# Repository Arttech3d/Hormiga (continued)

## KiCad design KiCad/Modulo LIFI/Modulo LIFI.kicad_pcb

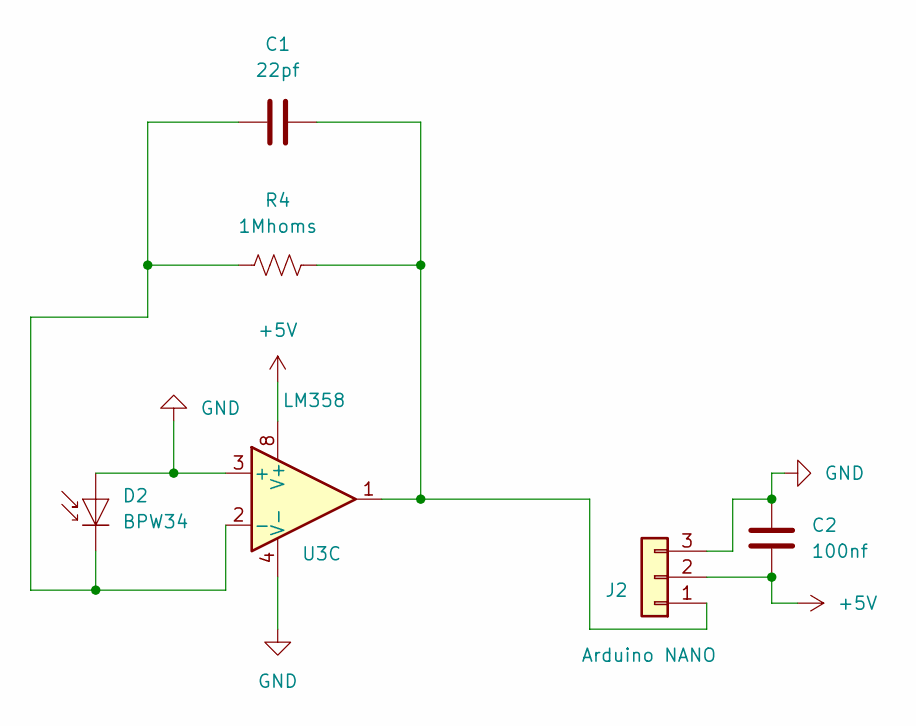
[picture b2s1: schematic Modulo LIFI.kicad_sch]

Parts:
C1: 22pf; C_Disc_D3.0mm_W1.6mm_P2.50mm
C2: 100nf; C_0805_2012Metric
D2: BPW34; Osram_BPW34S-SMD
J2: Arduino NANO; PinHeader_1x03_P2.54mm_Vertical
R4: 1Mhoms; R_0805_2012Metric_Pad1.20x1.40mm_HandSolder
U3: LM358; SOIC-8_3.9x4.9mm_P1.27mm

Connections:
+5V: C2.1, J2.2, U3.8 (V+)
GND: C2.2, D2.2 (A), J2.3, U3.3 (+), U3.4 (V-)
unnamed: C1.2, D2.1 (K), R4.2, U3.2 (-)
unnamed: C1.1, J2.1, R4.1, U3.1

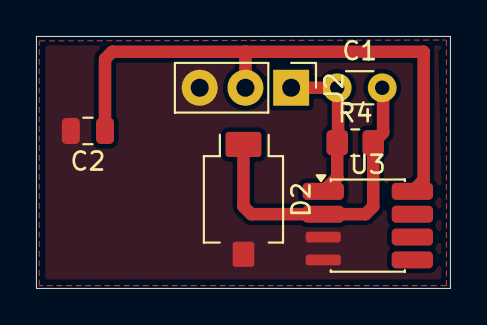
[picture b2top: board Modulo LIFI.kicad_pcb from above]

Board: 2 copper layers, 23.0 x 14.0 mm, 6 parts (0 on the bottom side), 4 nets.

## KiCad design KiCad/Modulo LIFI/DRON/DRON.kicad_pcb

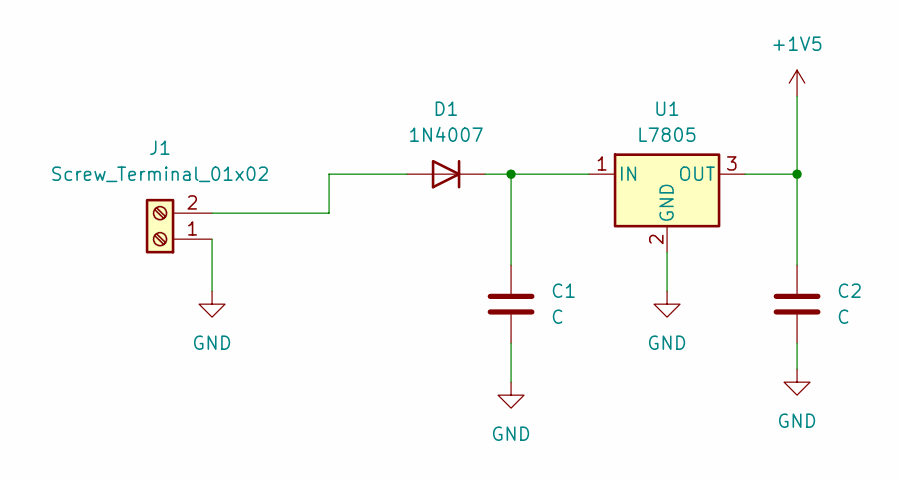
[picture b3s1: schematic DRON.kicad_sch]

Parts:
C1, C2: C; C_Disc_D3.0mm_W1.6mm_P2.50mm
D1: 1N4007; D_DO-41_SOD81_P10.16mm_Horizontal
J1: Screw_Terminal_01x02; TerminalBlock_MaiXu_MX126-5.0-02P_1x02_P5.00mm
U1: L7805; TO-220-3_Vertical

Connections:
+1V5: C2.1, U1.3 (OUT)
GND: C1.2, C2.2, J1.1, U1.2 (GND)
unnamed: D1.2 (A), J1.2
unnamed: C1.1, D1.1 (K), U1.1 (IN)

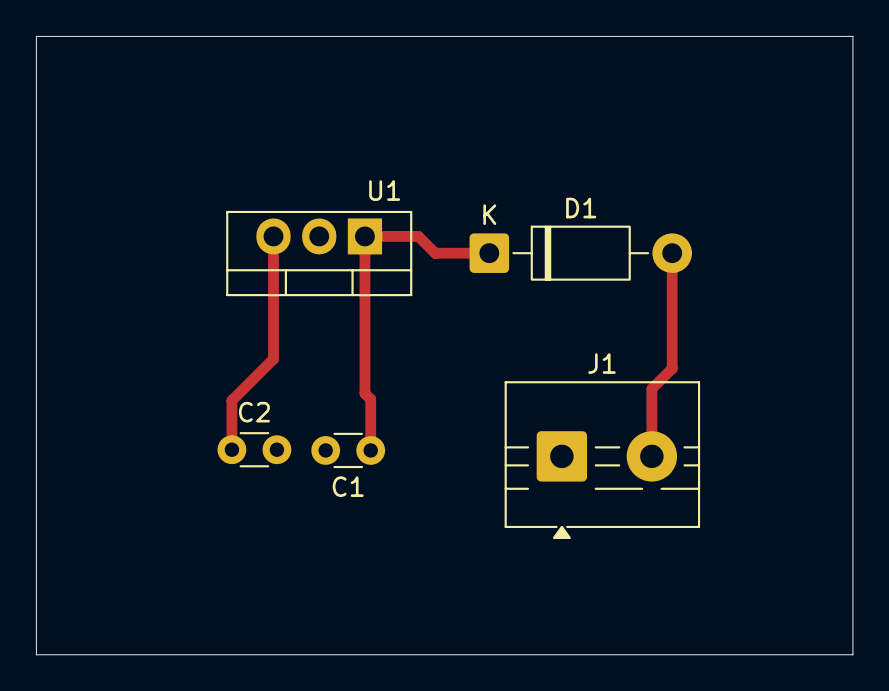
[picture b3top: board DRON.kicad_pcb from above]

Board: 2 copper layers, 45.4 x 34.4 mm, 5 parts (0 on the bottom side), 4 nets.

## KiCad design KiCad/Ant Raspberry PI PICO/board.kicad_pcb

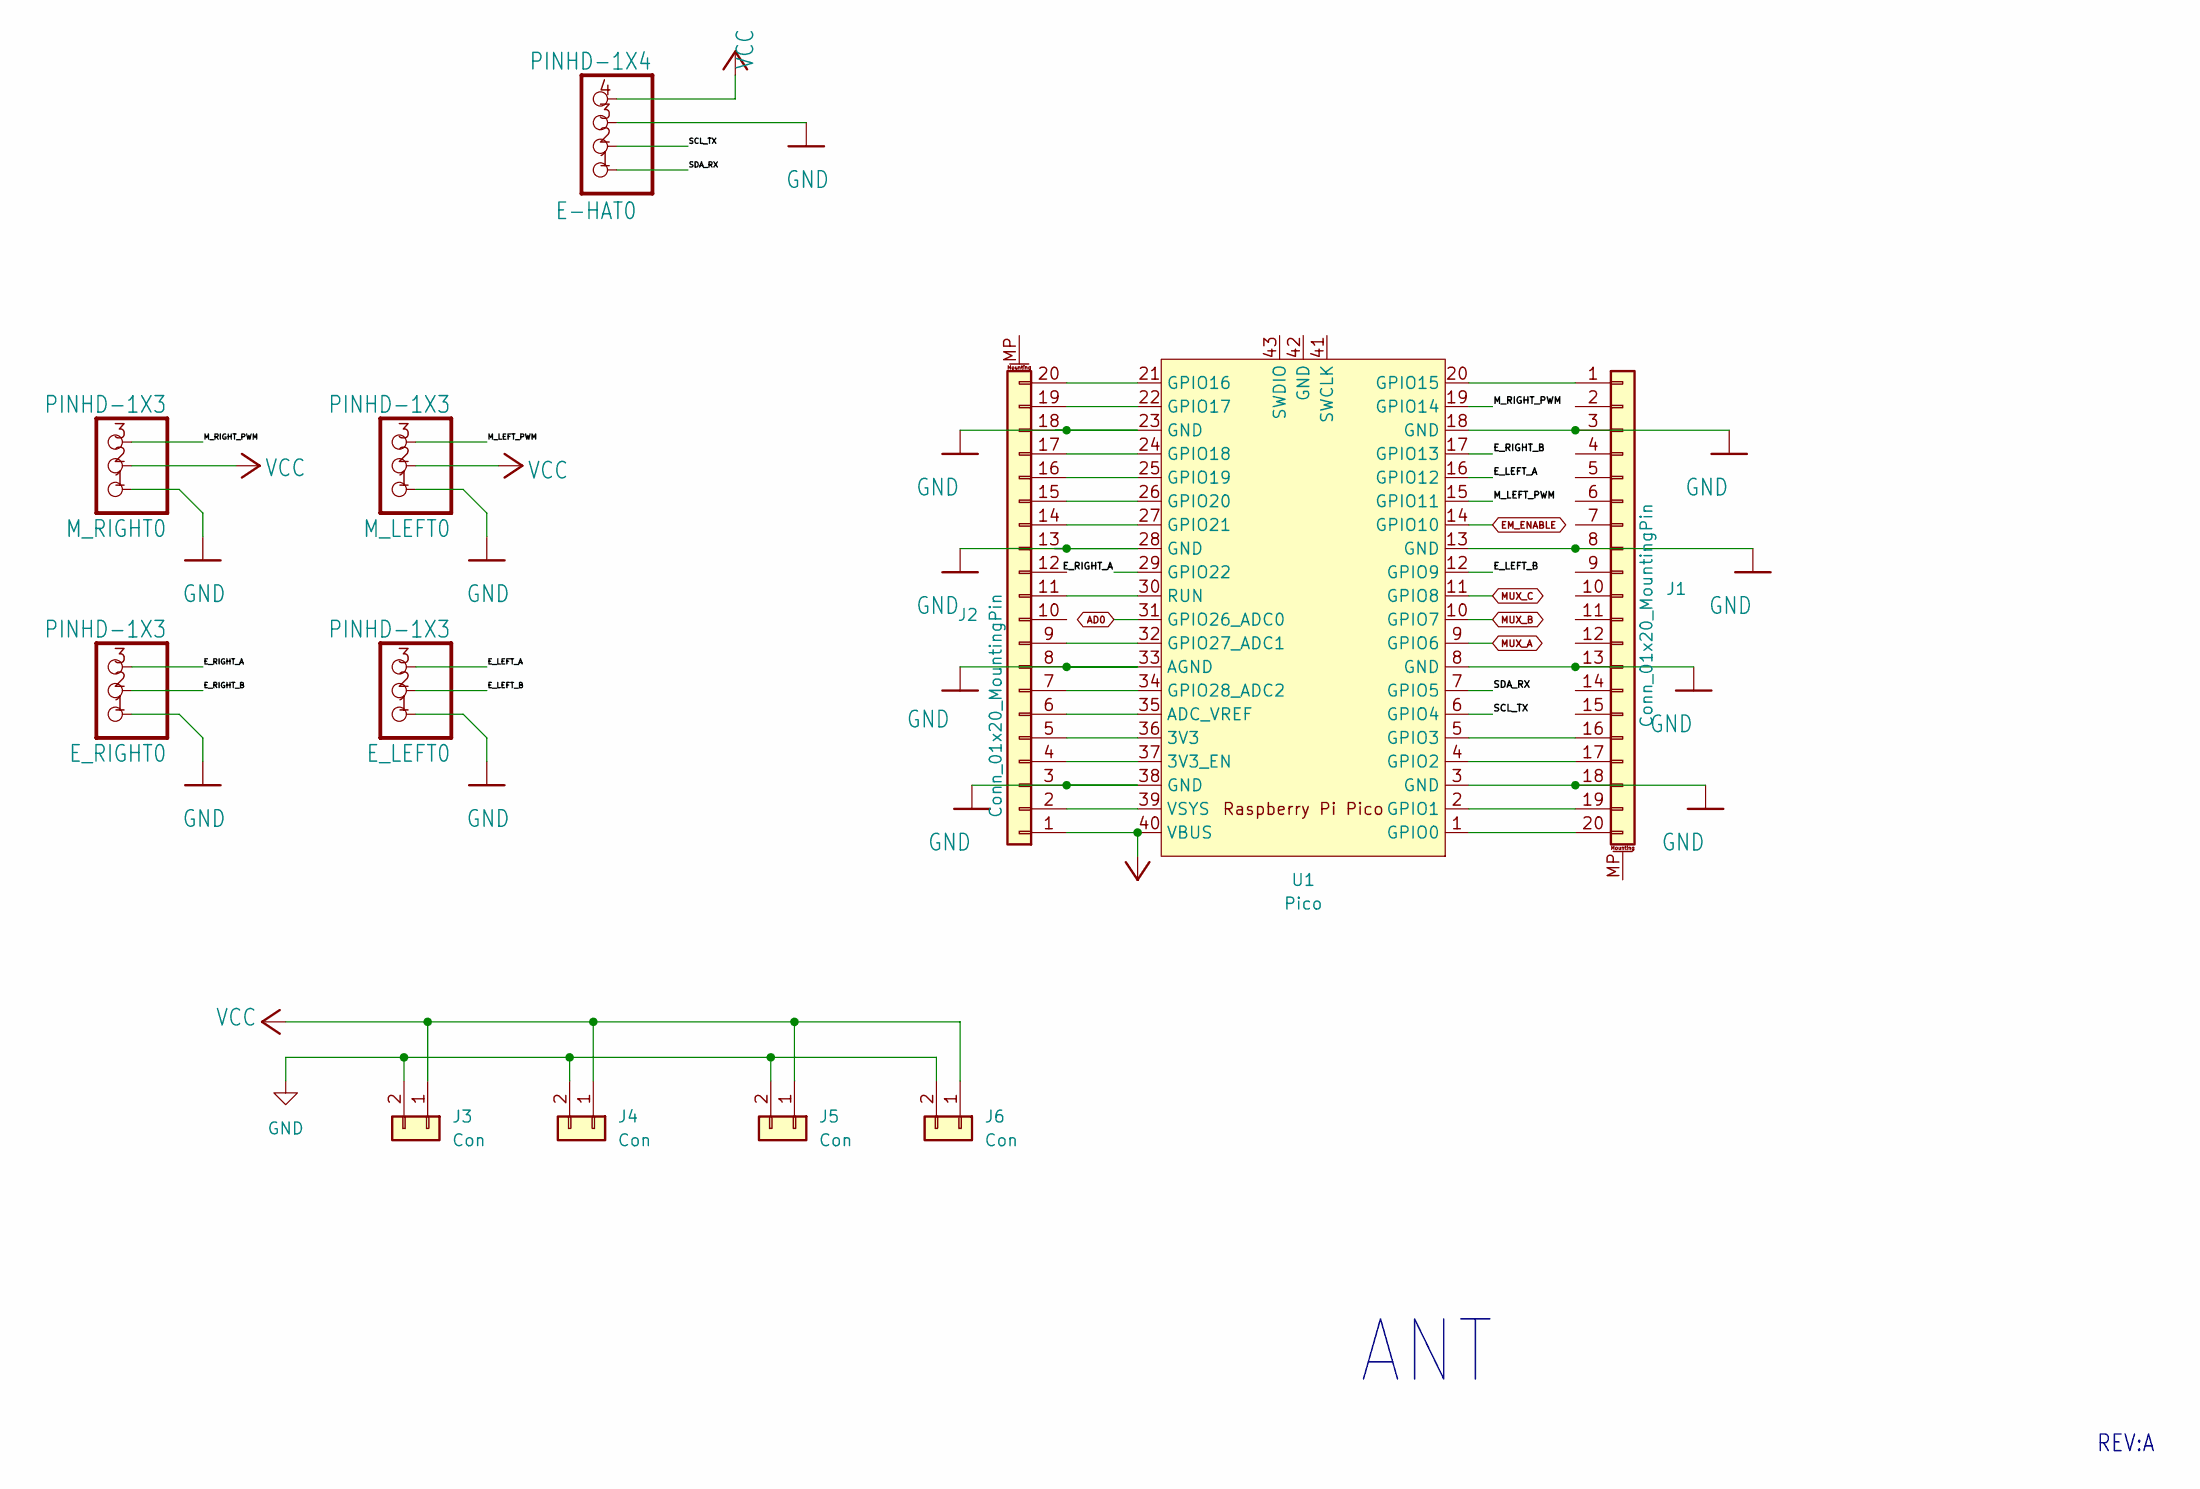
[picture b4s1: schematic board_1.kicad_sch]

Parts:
E-HAT0: PINHD-1X4; 1X04
E_LEFT0: PINHD-1X3; 1X03
E_RIGHT0: PINHD-1X3; 1X03
J1, J2: Conn_01x20_MountingPin; PinHeader_1x20_P2.54mm_Vertical
J3, J4, J5, J6: Con; PinHeader_1x02_P2.54mm_Vertical
M_LEFT0: PINHD-1X3; 1X03
M_RIGHT0: PINHD-1X3; 1X03
U1: Pico; RPi_Pico_SMD_TH

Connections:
/<p>MCU and Motors</p>/E_LEFT_A: E_LEFT0.3, U1.16 (GPIO12)
/<p>MCU and Motors</p>/E_LEFT_B: E_LEFT0.2, U1.12 (GPIO9)
/<p>MCU and Motors</p>/E_RIGHT_A: E_RIGHT0.3, U1.29 (GPIO22)
/<p>MCU and Motors</p>/E_RIGHT_B: E_RIGHT0.2, U1.17 (GPIO13)
/<p>MCU and Motors</p>/M_LEFT_PWM: M_LEFT0.3, U1.15 (GPIO11)
/<p>MCU and Motors</p>/M_RIGHT_PWM: M_RIGHT0.3, U1.19 (GPIO14)
/<p>MCU and Motors</p>/SCL_TX: E-HAT0.2, U1.6 (GPIO4)
/<p>MCU and Motors</p>/SDA_RX: E-HAT0.1, U1.7 (GPIO5)
AD0: U1.31 (GPIO26_ADC0); also elsewhere on the board
EM_ENABLE: U1.14 (GPIO10); also elsewhere on the board
GND: E-HAT0.3, E_LEFT0.1, E_RIGHT0.1, J1.3, J1.8, J1.13, J1.18, J2.3, J2.8, J2.13, J2.18, J3.2, J4.2, J5.2, J6.2, M_LEFT0.1, M_RIGHT0.1, U1.3 (GND), U1.8 (GND), U1.13 (GND), U1.18 (GND), U1.23 (GND), U1.28 (GND), U1.33 (AGND), U1.38 (GND); also elsewhere on the board
MUX_A: U1.9 (GPIO6); also elsewhere on the board
MUX_B: U1.10 (GPIO7); also elsewhere on the board
MUX_C: U1.11 (GPIO8); also elsewhere on the board
unnamed: J1.1, U1.20 (GPIO15)
unnamed: J1.16, U1.5 (GPIO3)
unnamed: J1.17, U1.4 (GPIO2)
unnamed: J1.19, U1.2 (GPIO1)
unnamed: J1.20, U1.1 (GPIO0)
unnamed: J2.2, U1.39 (VSYS)
unnamed: J2.4, U1.37 (3V3_EN)
unnamed: J2.5, U1.36 (3V3)
unnamed: J2.6, U1.35 (ADC_VREF)
unnamed: J2.7, U1.34 (GPIO28_ADC2)
unnamed: J2.9, U1.32 (GPIO27_ADC1)
unnamed: J2.11, U1.30 (RUN)
unnamed: J2.14, U1.27 (GPIO21)
unnamed: J2.15, U1.26 (GPIO20)
unnamed: J2.16, U1.25 (GPIO19)
unnamed: J2.17, U1.24 (GPIO18)
unnamed: J2.19, U1.22 (GPIO17)
unnamed: J2.20, U1.21 (GPIO16)
VCC: E-HAT0.4, J2.1, J3.1, J4.1, J5.1, J6.1, M_LEFT0.2, M_RIGHT0.2, U1.40 (VBUS); also elsewhere on the board

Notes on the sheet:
ANT
REV:A

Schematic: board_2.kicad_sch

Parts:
IRLML2502: MOSFET-NREFLOW; SOT23
MUX0: 4051D; SO16
P0, P1, P2, P3, P4, P5, P6, P7: TCRT5000
R0, R1, R2, R3, R4, R5, R6, R7: 4k7; M0805
R8: 4k7; R0805
R9: 0R; R0805
R10: 18R; R0805
R11: NM; R0805

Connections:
/<p>Proximity Sensors</p>/EM: P0.K (CATHODE), P1.K (CATHODE), P2.K (CATHODE), P3.K (CATHODE), P4.K (CATHODE), P5.K (CATHODE), P6.K (CATHODE), P7.K (CATHODE), R9.2, R11.2
/<p>Proximity Sensors</p>/MUX_X0: MUX0.13 (X0), P0.E (EMITTER), R4.1
/<p>Proximity Sensors</p>/MUX_X1: MUX0.14 (X1), P1.E (EMITTER), R5.1
/<p>Proximity Sensors</p>/MUX_X2: MUX0.15 (X2), P2.E (EMITTER), R6.1
/<p>Proximity Sensors</p>/MUX_X3: MUX0.12 (X3), P3.E (EMITTER), R3.1
/<p>Proximity Sensors</p>/MUX_X4: MUX0.1 (X4), P4.E (EMITTER), R7.1
/<p>Proximity Sensors</p>/MUX_X5: MUX0.5 (X5), P5.E (EMITTER), R2.1
/<p>Proximity Sensors</p>/MUX_X6: MUX0.2 (X6), P6.E (EMITTER), R0.1
/<p>Proximity Sensors</p>/MUX_X7: MUX0.4 (X7), P7.E (EMITTER), R1.1
AD0: MUX0.3 (X); also elsewhere on the board
EM_ENABLE: R8.2; also elsewhere on the board
GND: IRLML2502.2 (S), MUX0.6 (INH), MUX0.7 (VEE), MUX0.8 (GND), R0.2, R1.2, R2.2, R3.2, R4.2, R5.2, R6.2, R7.2; also elsewhere on the board
MUX_A: MUX0.11 (A); also elsewhere on the board
MUX_B: MUX0.10 (B); also elsewhere on the board
MUX_C: MUX0.9 (C); also elsewhere on the board
unnamed: IRLML2502.3 (D), R10.1
unnamed: IRLML2502.1 (G), R8.1
unnamed: R9.1, R10.2, R11.1
VCC: MUX0.16 (VCC), P0.A (ANODE), P0.C (COLLECTOR), P1.A (ANODE), P1.C (COLLECTOR), P2.A (ANODE), P2.C (COLLECTOR), P3.A (ANODE), P3.C (COLLECTOR), P4.A (ANODE), P4.C (COLLECTOR), P5.A (ANODE), P5.C (COLLECTOR), P6.A (ANODE), P6.C (COLLECTOR), P7.A (ANODE), P7.C (COLLECTOR); also elsewhere on the board

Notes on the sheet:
HeRo v2.7 VeRLab
REV:A

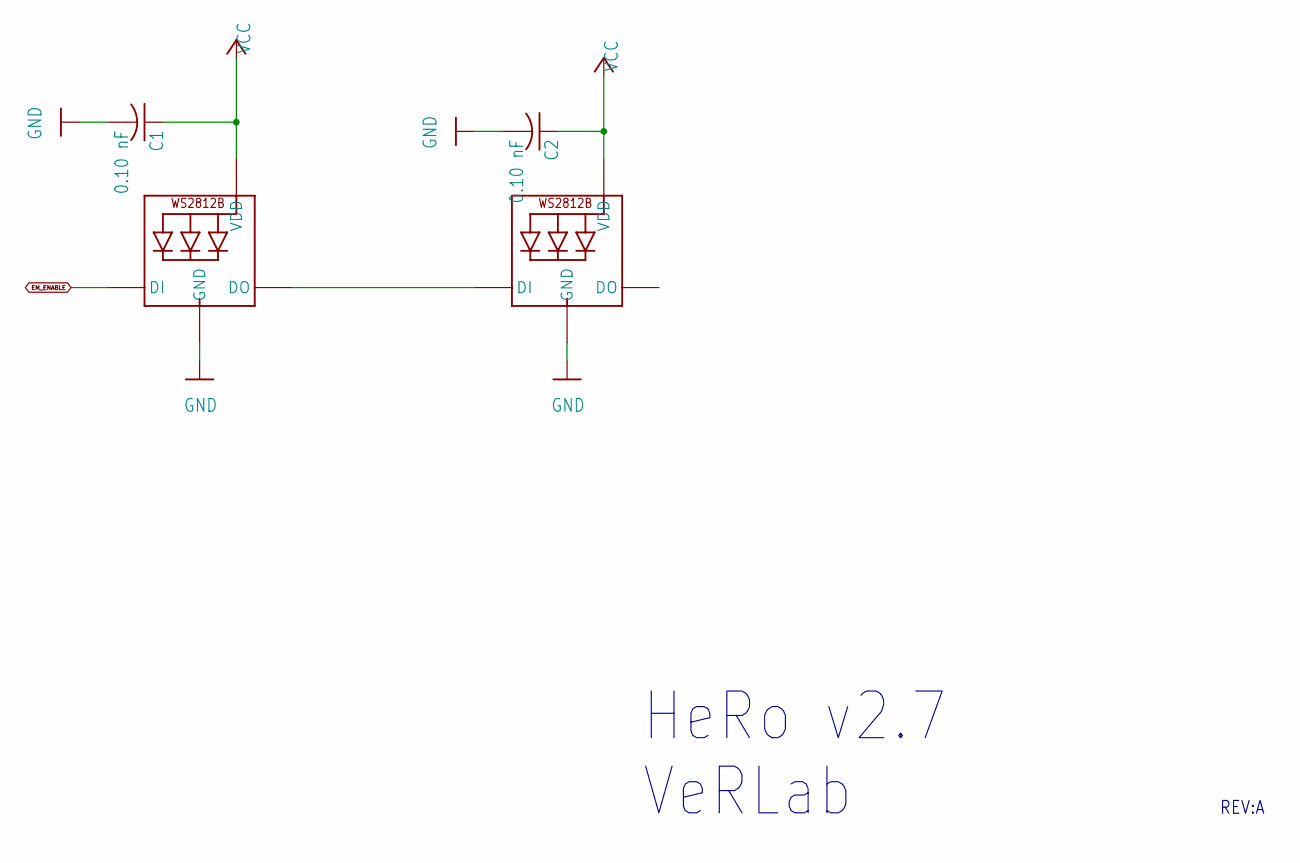
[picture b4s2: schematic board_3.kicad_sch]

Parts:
C1, C2: 0.10 nF; C0603_348
LED0, LED1: WS2812B5050; WS2812B

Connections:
EM_ENABLE: LED0.4-DIN (DI); also elsewhere on the board
GND: C1.2, C2.2, LED0.3-GND (GND), LED1.3-GND (GND); also elsewhere on the board
unnamed: LED0.2-DOUT (DO), LED1.4-DIN (DI)
VCC: C1.1, C2.1, LED0.1-VDD (VDD), LED1.1-VDD (VDD); also elsewhere on the board

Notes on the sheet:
HeRo v2.7 VeRLab
REV:A

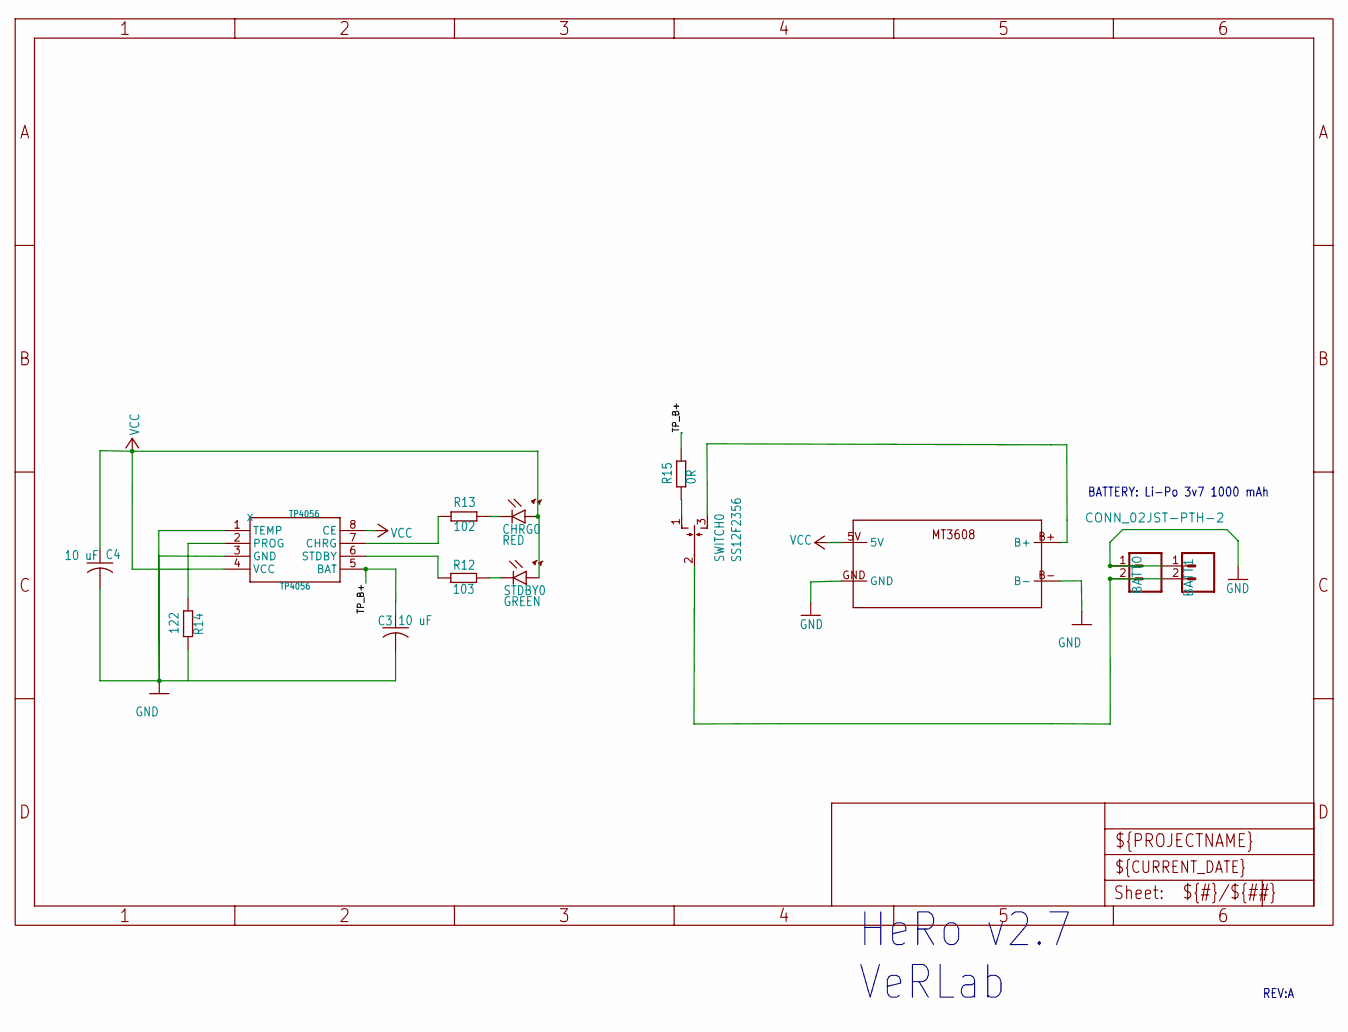
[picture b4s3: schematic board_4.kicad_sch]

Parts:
BATT0, BATT1: CONN_02JST-PTH-2; JST-2-PTH
C3, C4: 10 uF; C0603_420
CHRG0: RED; SML0805
MT3608: MT3608
R12: 103; R0805
R13: 102; R0805
R14: 122; R0603
R15: 0R; R0805
STDBY0: GREEN; SML0805
SWITCH0: SS12F2356; HH3T90
TP4056: TP4056; SOP

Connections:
/<p>Power Supply</p>/TP_B+: C3.1, R15.2, TP4056.5 (BAT)
GND: BATT0.1, BATT1.1, C3.2, C4.2, MT3608.B-, MT3608.GND, TP4056.1 (TEMP), TP4056.3 (GND); also elsewhere on the board
unnamed: CHRG0.C, R13.2
unnamed: R12.2, STDBY0.C
unnamed: R15.1, SWITCH0.1 (O)
unnamed: BATT0.2, BATT1.2, SWITCH0.2
unnamed: MT3608.B+, SWITCH0.3 (S)
unnamed: R13.1, TP4056.7 (CHRG)
unnamed: R14.2, TP4056.2 (PROG)
unnamed: R12.1, TP4056.6 (STDBY)
VCC: C4.1, CHRG0.A, MT3608.5V, STDBY0.A, TP4056.4 (VCC), TP4056.8 (CE); also elsewhere on the board

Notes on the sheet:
REV:A
HeRo v2.7 VeRLab
BATTERY: Li-Po 3v7 1000 mAh

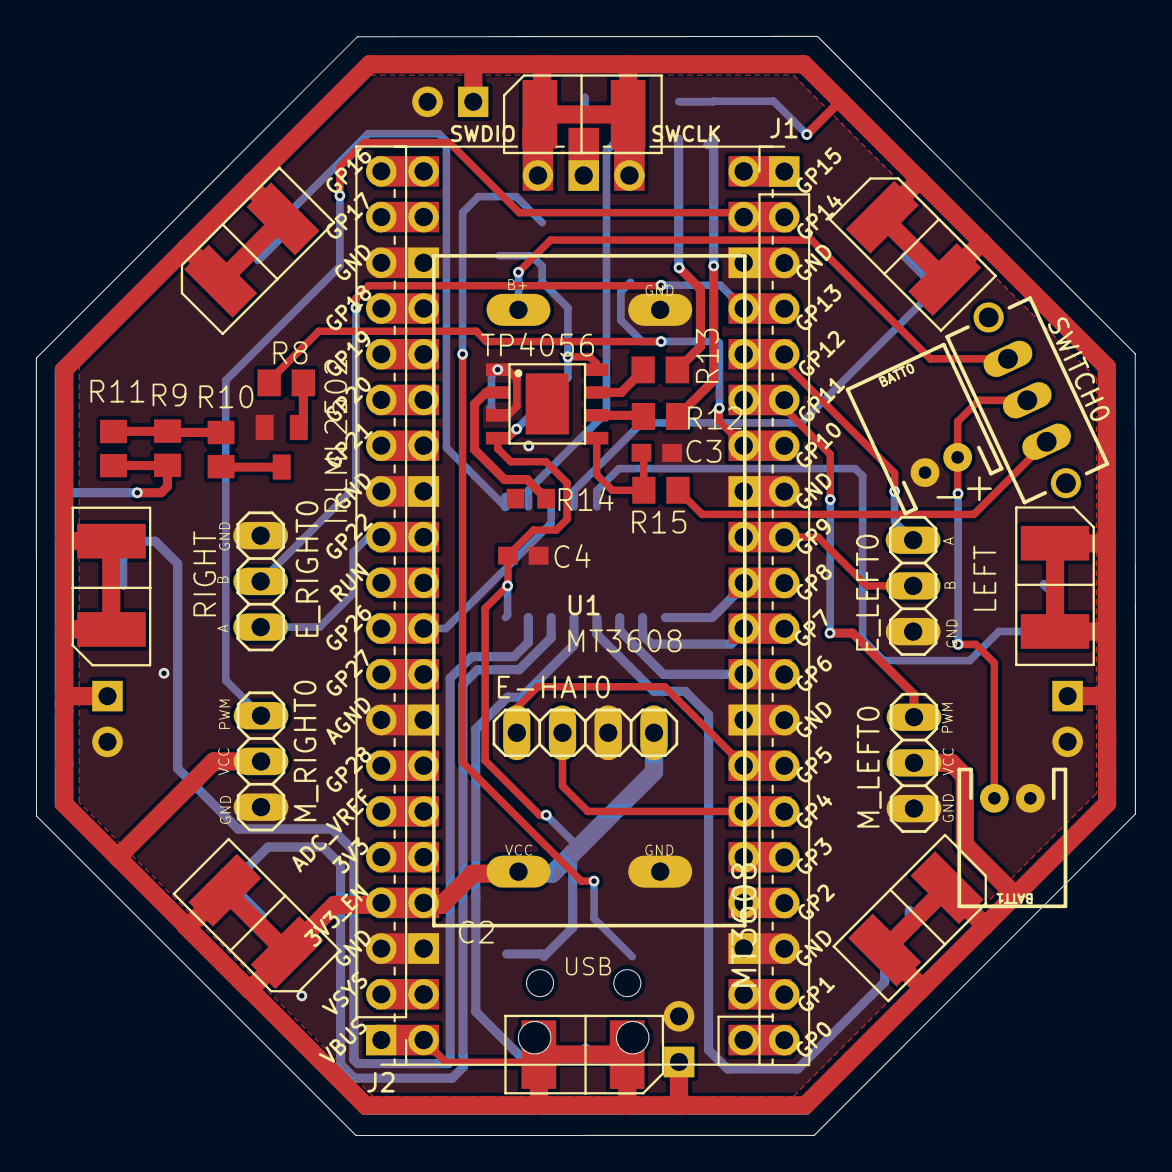
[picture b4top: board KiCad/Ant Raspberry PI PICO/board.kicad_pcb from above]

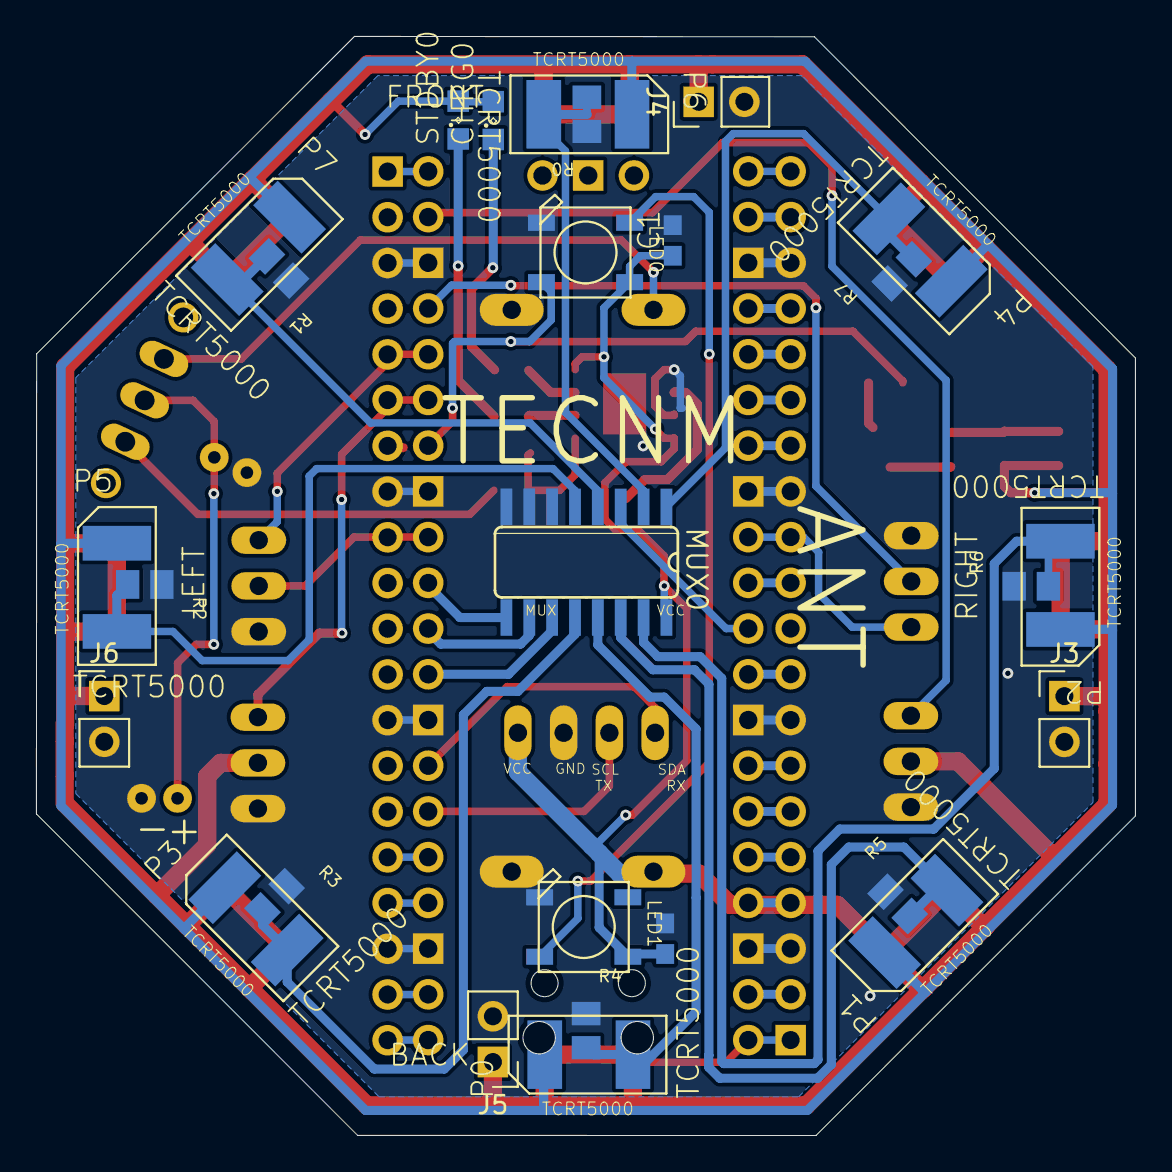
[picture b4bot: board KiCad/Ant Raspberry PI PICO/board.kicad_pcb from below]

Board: 2 copper layers, 61.1 x 61.1 mm, 51 parts (27 on the bottom side), 55 nets.

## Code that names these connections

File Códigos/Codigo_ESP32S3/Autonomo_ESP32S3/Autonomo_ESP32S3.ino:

// Código ESP32-s3
#include <ESP32Servo.h>

/************************************************************************
 * CONFIGURACIÓN DEL MULTIPLEXOR Y SENSORES
 ************************************************************************/
#define MUX_A_PIN 21  // GPIO21
#define MUX_B_PIN 47  // GPIO47
#define MUX_C_PIN 45  // GPIO45
#define MUX_EN_PIN 48  // GPIO48
#define SENSOR_COUNT 8
#define A0 7           /* ADC ESP32-S3 */

const int real_pos[8] = {0,1,2,7,3,6,4,5};
float sensor_readings[SENSOR_COUNT];

#define PROXIMITY_THRESH 40  // Umbral de detección

/************************************************************************
 * CONFIGURACIÓN DE LOS MOTORES
 ************************************************************************/
#define WHEEL_R_PIN 1     // GPIO1
#define WHEEL_L_PIN 41    // GPIO41
#define WHEEL_R_MID 1590
#define WHEEL_L_MID 1590

// Variables de velocidad individual
int VELDR = 220;  // Velocidad motor derecho
int VELIZ = 100;  // Velocidad motor izquierdo

Servo wheel_right, wheel_left;

/************************************************************************
 * FUNCIONES DEL MULTIPLEXOR Y SENSORES
 ************************************************************************/
void selectInput(int input) {
  digitalWrite(MUX_A_PIN, input & 0x01);
  digitalWrite(MUX_B_PIN, (input >> 1) & 0x01);
  digitalWrite(MUX_C_PIN, (input >> 2) & 0x01);
}

float readSensor() {
  delayMicroseconds(500);
  float env = (float)analogRead(A0);
  analogWrite(MUX_EN_PIN, 1023);
  delayMicroseconds(100);
  float sensor_reading = (float)analogRead(A0) - env;
  analogWrite(MUX_EN_PIN, 0);
  if (sensor_reading < 0) sensor_reading = 1;
  return sensor_reading;
}

void readSensors() {
  Serial.println("\nLeyendo sensores...");
  for (int i = 0; i < SENSOR_COUNT; i++) {
    selectInput(i);
    sensor_readings[real_pos[i]] = readSensor();
    Serial.print("Sensor ");
    Serial.print(i);
    Serial.print(": ");
    Serial.println(sensor_readings[real_pos[i]]);
  }
}

/************************************************************************
 * CONTROL DE MOVIMIENTO AUTÓNOMO
 ************************************************************************/
void updateVelocities() {
  bool obst_front   = sensor_readings[0] >= PROXIMITY_THRESH;
  bool obst_fleft   = sensor_readings[1] >= PROXIMITY_THRESH;
  bool obst_left    = sensor_readings[2] >= PROXIMITY_THRESH;
  bool obst_bleft   = sensor_readings[3] >= PROXIMITY_THRESH;
  bool obst_back    = sensor_readings[4] >= PROXIMITY_THRESH;
  bool obst_bright  = sensor_readings[5] >= PROXIMITY_THRESH;
  bool obst_right   = sensor_readings[6] >= PROXIMITY_THRESH;
  bool obst_fright  = sensor_readings[7] >= PROXIMITY_THRESH;

  Serial.println("\n--- Análisis de obstáculos ---");
  if (obst_front || obst_fright || obst_fleft) {
    Serial.println("Obstáculo detectado al frente. Girando...");
    float sum_left  = sensor_readings[1] + sensor_readings[2] + sensor_readings[3];
    float sum_right = sensor_readings[7] + sensor_readings[6] + sensor_readings[5];

    if (sum_left < sum_right) {
      Serial.println("Giro a la izquierda.");
      wheel_right.writeMicroseconds(WHEEL_R_MID + VELDR);
      wheel_left.writeMicroseconds(WHEEL_L_MID + VELIZ);
    } else {
      Serial.println("Giro a la derecha.");
      wheel_right.writeMicroseconds(WHEEL_R_MID - VELDR);
      wheel_left.writeMicroseconds(WHEEL_L_MID - VELIZ);
    }
  }
  else if (obst_left || obst_bleft) {
    Serial.println("Obstáculo a la izquierda. Girando a la derecha...");
    wheel_right.writeMicroseconds(WHEEL_R_MID - VELDR);
    wheel_left.writeMicroseconds(WHEEL_L_MID - VELIZ);
  }
  else if (obst_right || obst_bright) {
    Serial.println("Obstáculo a la derecha. Girando a la izquierda...");
    wheel_right.writeMicroseconds(WHEEL_R_MID + VELDR);
    wheel_left.writeMicroseconds(WHEEL_L_MID + VELIZ);
  }
  else if (obst_back) {
    Serial.println("Obstáculo detrás. Avanzando hacia adelante...");
    wheel_right.writeMicroseconds(WHEEL_R_MID - VELDR - 50);
    wheel_left.writeMicroseconds(WHEEL_L_MID + VELIZ + 50);
  }
  else {
    Serial.println("Sin obstáculos. Avanzando hacia adelante...");
    wheel_right.writeMicroseconds(WHEEL_R_MID - VELDR);
    wheel_left.writeMicroseconds(WHEEL_L_MID + VELIZ);
  }
}

/************************************************************************
 * SETUP
 ************************************************************************/
void setup() {
  pinMode(MUX_A_PIN, OUTPUT);
  pinMode(MUX_B_PIN, OUTPUT);
  pinMode(MUX_C_PIN, OUTPUT);
  pinMode(MUX_EN_PIN, OUTPUT);
  analogWrite(MUX_EN_PIN, 0);

  wheel_right.attach(WHEEL_R_PIN);
  wheel_left.attach(WHEEL_L_PIN);
  wheel_right.writeMicroseconds(WHEEL_R_MID);
  wheel_left.writeMicroseconds(WHEEL_L_MID);

  Serial.begin(115200);
  Serial.println("=======================================");
  Serial.println("   Robot autónomo iniciado correctamente");
  Serial.println("   Escaneando entorno y ajustando ruta...");
  Serial.println("=======================================");
  Serial.println("Usa VELDR y VELIZ para ajustar la velocidad individual de los motores.\n");
}

/************************************************************************
 * LOOP PRINCIPAL
 ************************************************************************/
void loop() {
  Serial.println("\n--------------------------------------");
  Serial.println("Lectura de sensores y control de movimiento");
  Serial.println("--------------------------------------");
  readSensors();
  updateVelocities();
  delay(500);
}

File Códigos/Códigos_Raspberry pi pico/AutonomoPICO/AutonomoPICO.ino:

// Código PICO
#include <Servo.h>

/************************************************************************
 * CONFIGURACIÓN DEL MULTIPLEXOR Y SENSORES
 ************************************************************************/
#define MUX_A_PIN 6   // GPIO6
#define MUX_B_PIN 7   // GPIO7
#define MUX_C_PIN 8   // GPIO8
#define MUX_EN_PIN 10 // GPIO10
#define SENSOR_COUNT 8

const int real_pos[8] = {0, 1, 2, 7, 3, 6, 4, 5};
float sensor_readings[SENSOR_COUNT];

#define PROXIMITY_THRESH 40  // Umbral de detección
#define SENSOR_ADC_PIN 26    // GPIO26 = ADC0 en la Raspberry Pi Pico

/************************************************************************
 * CONFIGURACIÓN DE LOS MOTORES
 ************************************************************************/
#define WHEEL_R_PIN  14   // GPIO14
#define WHEEL_L_PIN  11   // GPIO11
#define WHEEL_R_MID 1590
#define WHEEL_L_MID 1590

// Variables de velocidad individual
int VELDR = 220;  // Velocidad motor derecho
int VELIZ = 100;  // Velocidad motor izquierdo

Servo wheel_right, wheel_left;

/************************************************************************
 * FUNCIONES DEL MULTIPLEXOR Y SENSORES
 ************************************************************************/
void selectInput(int input) {
  digitalWrite(MUX_A_PIN, input & 0x01);
  digitalWrite(MUX_B_PIN, (input >> 1) & 0x01);
  digitalWrite(MUX_C_PIN, (input >> 2) & 0x01);
}

float readSensor() {
  delayMicroseconds(500);
  
  // Lectura ambiental (emisores apagados)
  float env = analogRead(SENSOR_ADC_PIN);
  
  // Encender emisores
  digitalWrite(MUX_EN_PIN, HIGH);
  delayMicroseconds(100);
  
  // Lectura con emisores encendidos
  float sensor_reading = analogRead(SENSOR_ADC_PIN) - env;
  
  // Apagar emisores
  digitalWrite(MUX_EN_PIN, LOW);

  // Evitar valores negativos
  if (sensor_reading < 0) sensor_reading = 1;
  return sensor_reading;
}

void readSensors() {
  Serial.println("\nLeyendo sensores...");
  for (int i = 0; i < SENSOR_COUNT; i++) {
    selectInput(i);
    sensor_readings[real_pos[i]] = readSensor();
    Serial.print("Sensor ");
    Serial.print(i);
    Serial.print(": ");
    Serial.println(sensor_readings[real_pos[i]]);
  }
}

/************************************************************************
 * CONTROL DE MOVIMIENTO AUTÓNOMO
 ************************************************************************/
void updateVelocities() {
  bool obst_front   = sensor_readings[0] >= PROXIMITY_THRESH;
  bool obst_fleft   = sensor_readings[1] >= PROXIMITY_THRESH;
  bool obst_left    = sensor_readings[2] >= PROXIMITY_THRESH;
  bool obst_bleft   = sensor_readings[3] >= PROXIMITY_THRESH;
  bool obst_back    = sensor_readings[4] >= PROXIMITY_THRESH;
  bool obst_bright  = sensor_readings[5] >= PROXIMITY_THRESH;
  bool obst_right   = sensor_readings[6] >= PROXIMITY_THRESH;
  bool obst_fright  = sensor_readings[7] >= PROXIMITY_THRESH;

  Serial.println("\n--- Análisis de obstáculos ---");
  if (obst_front || obst_fright || obst_fleft) {
    Serial.println("Obstáculo detectado al frente. Girando...");
    float sum_left  = sensor_readings[1] + sensor_readings[2] + sensor_readings[3];
    float sum_right = sensor_readings[7] + sensor_readings[6] + sensor_readings[5];

    if (sum_left < sum_right) {
      Serial.println("Giro a la izquierda.");
      wheel_right.writeMicroseconds(WHEEL_R_MID + VELDR);
      wheel_left.writeMicroseconds(WHEEL_L_MID + VELIZ);
    } else {
      Serial.println("Giro a la derecha.");
      wheel_right.writeMicroseconds(WHEEL_R_MID - VELDR);
      wheel_left.writeMicroseconds(WHEEL_L_MID - VELIZ);
    }
  }
  else if (obst_left || obst_bleft) {
    Serial.println("Obstáculo a la izquierda. Girando a la derecha...");
    wheel_right.writeMicroseconds(WHEEL_R_MID - VELDR);
    wheel_left.writeMicroseconds(WHEEL_L_MID - VELIZ);
  }
  else if (obst_right || obst_bright) {
    Serial.println("Obstáculo a la derecha. Girando a la izquierda...");
    wheel_right.writeMicroseconds(WHEEL_R_MID + VELDR);
    wheel_left.writeMicroseconds(WHEEL_L_MID + VELIZ);
  }
  else if (obst_back) {
    Serial.println("Obstáculo detrás. Avanzando hacia adelante...");
    wheel_right.writeMicroseconds(WHEEL_R_MID - VELDR - 50);
    wheel_left.writeMicroseconds(WHEEL_L_MID + VELIZ + 50);
  }
  else {
    Serial.println("Sin obstáculos. Avanzando hacia adelante...");
    wheel_right.writeMicroseconds(WHEEL_R_MID - VELDR);
    wheel_left.writeMicroseconds(WHEEL_L_MID + VELIZ);
  }
}

/************************************************************************
 * SETUP
 ************************************************************************/
void setup() {
  pinMode(MUX_A_PIN, OUTPUT);
  pinMode(MUX_B_PIN, OUTPUT);
  pinMode(MUX_C_PIN, OUTPUT);
  pinMode(MUX_EN_PIN, OUTPUT);
  digitalWrite(MUX_EN_PIN, LOW);

  wheel_right.attach(WHEEL_R_PIN);
  wheel_left.attach(WHEEL_L_PIN);
  wheel_right.writeMicroseconds(WHEEL_R_MID);
  wheel_left.writeMicroseconds(WHEEL_L_MID);

  Serial.begin(115200);
  Serial.println("=======================================");
  Serial.println("   Robot autónomo iniciado correctamente");
  Serial.println("   Escaneando entorno y ajustando ruta...");
  Serial.println("=======================================");
  Serial.println("Usa VELDR y VELIZ para ajustar la velocidad individual de los motores.\n");
}

/************************************************************************
 * LOOP PRINCIPAL
 ************************************************************************/
void loop() {
  Serial.println("\n--------------------------------------");
  Serial.println("Lectura de sensores y control de movimiento");
  Serial.println("--------------------------------------");
  readSensors();
  updateVelocities();
  delay(500);
}

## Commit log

2025-12-08 nuevo repositorio
2025-12-09 Actualizando documentos
2025-12-14 Actualización de archivos
2025-12-20 Descripción de los cambios
2026-01-14 Mensaje describiendo tus cambios
